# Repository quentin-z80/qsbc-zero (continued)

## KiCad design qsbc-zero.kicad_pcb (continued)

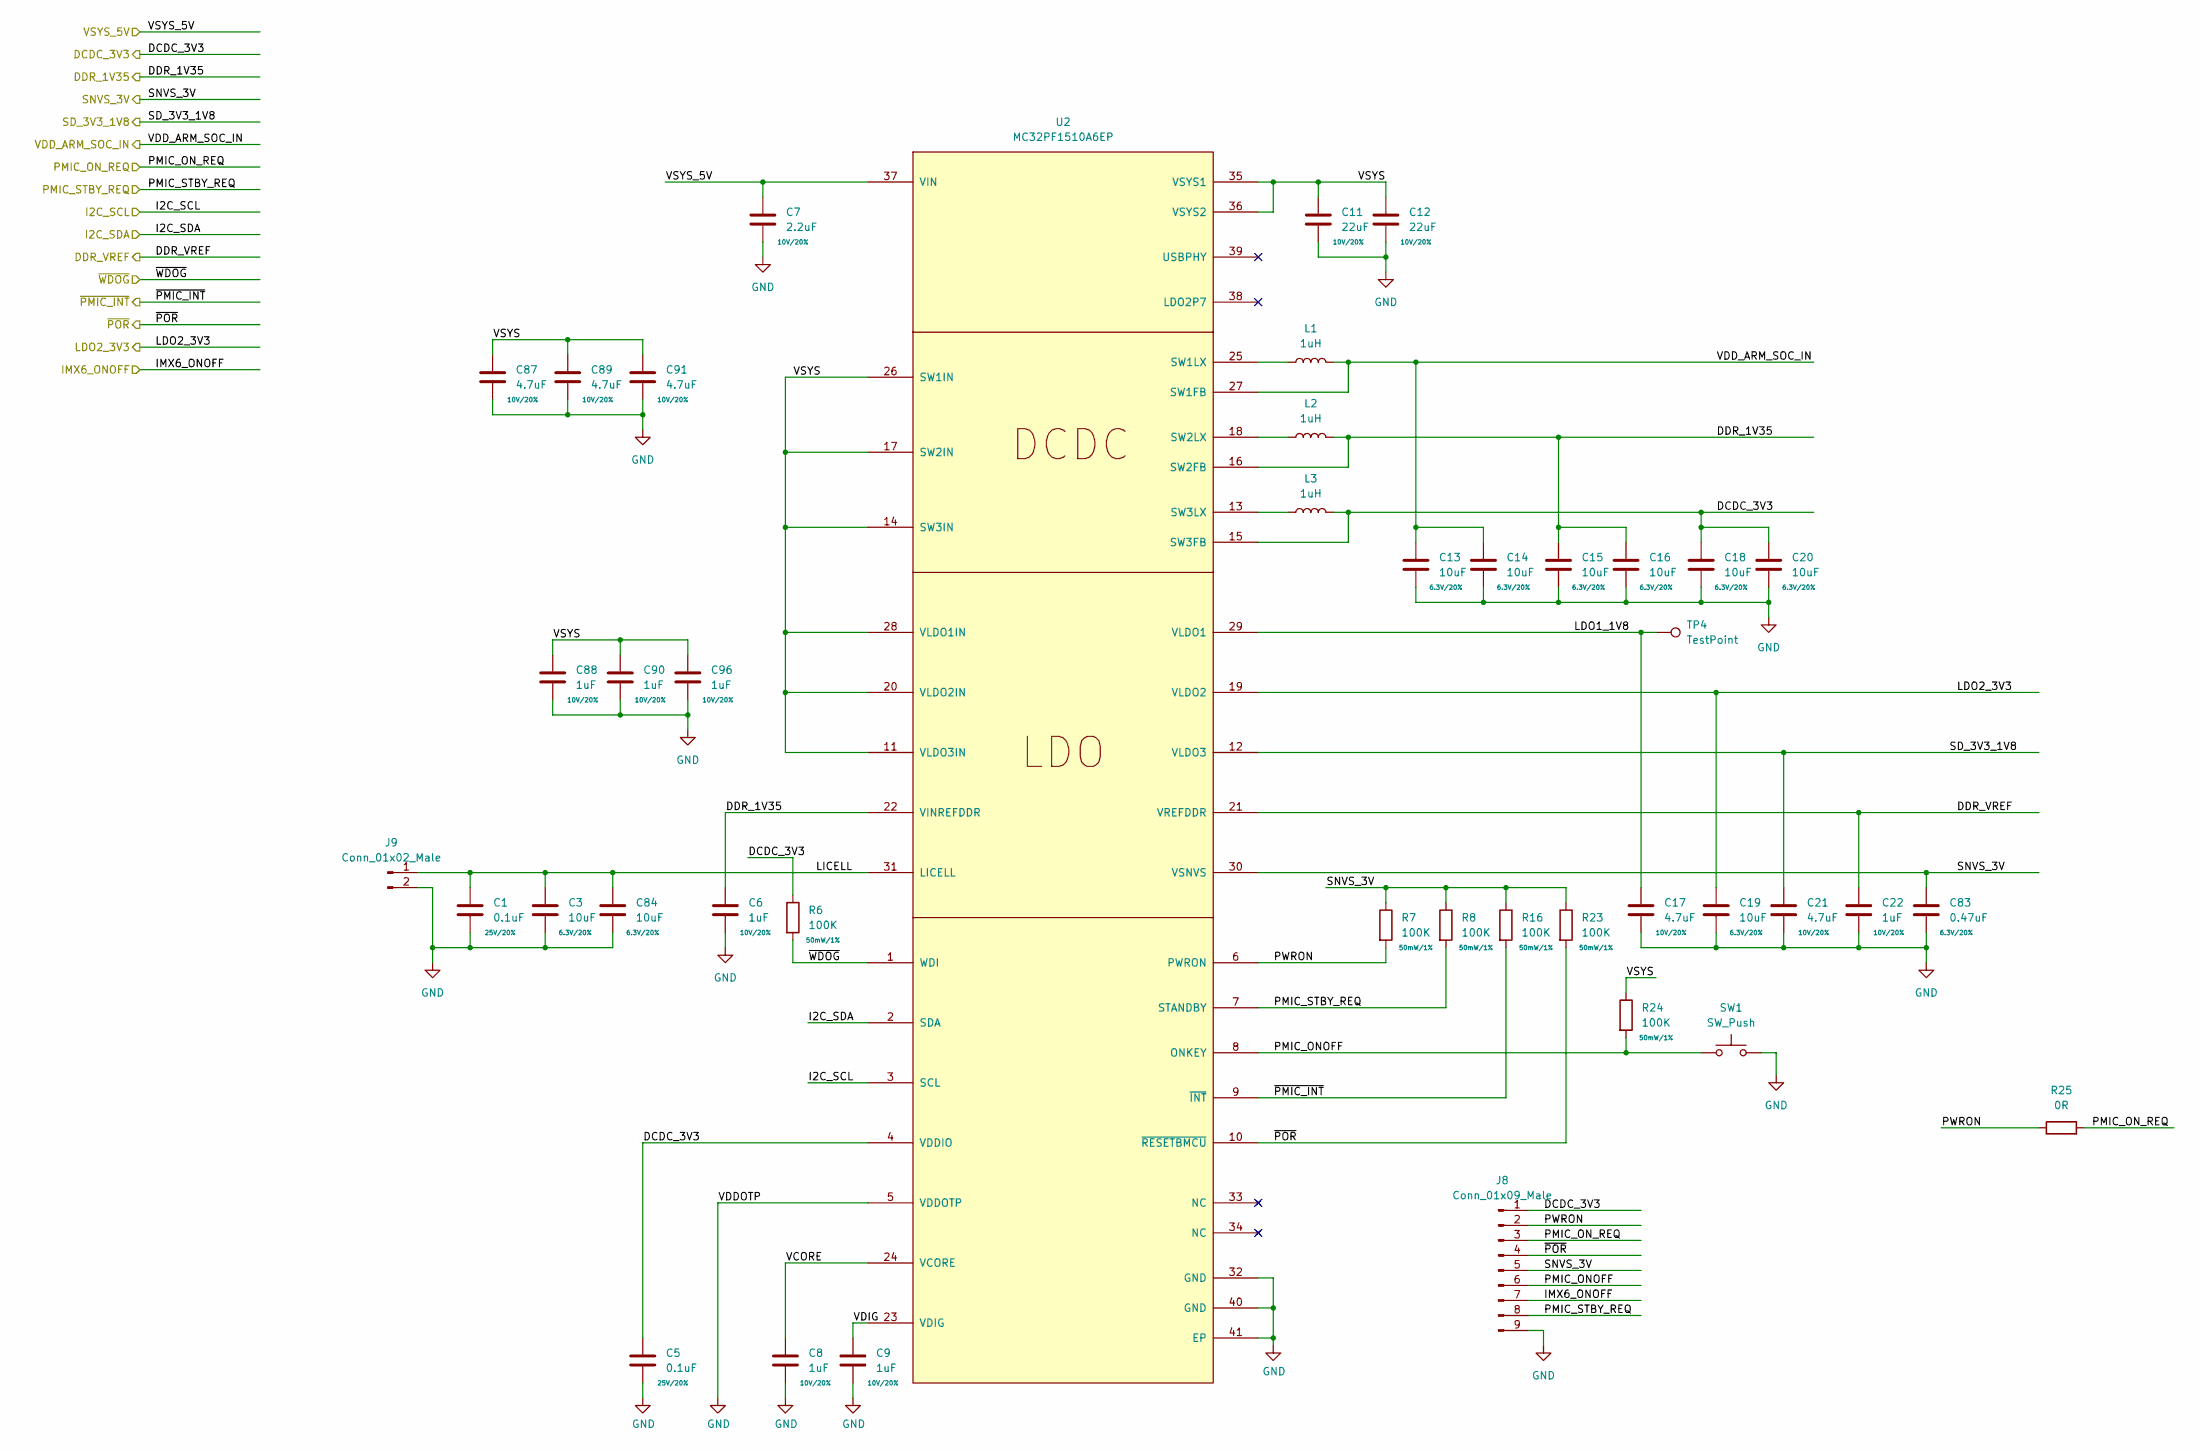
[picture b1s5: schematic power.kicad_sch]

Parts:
C1, C5: 0.1uF; C_0402_1005Metric; Rating 25V/20%; MPN GRM155R71E104KE14J; DigiKey_PN 490-14603-1-ND
C3, C13, C14, C15, C16, C18, C19, C20, C84: 10uF; C_0402_1005Metric; Rating 6.3V/20%; MPN GRM155R60J106ME05D; DigiKey_PN 490-GRM155R60J106ME05DCT-ND
C6, C8, C9, C22, C88, C90, C96: 1uF; C_0402_1005Metric; Rating 10V/20%; MPN GCM155C71A105KE38D; DigiKey_PN 490-13409-1-ND
C7: 2.2uF; C_0402_1005Metric; Rating 10V/20%; MPN CL05A225MP5NSNC; DigiKey_PN 1276-1467-1-ND
C11, C12: 22uF; C_0603_1608Metric; Rating 10V/20%; MPN CL10A226MP8NUNE; DigiKey_PN 1276-1274-1-ND
C17, C21, C87, C89, C91: 4.7uF; C_0402_1005Metric; Rating 10V/20%; MPN CL05A475MP5NRNC; DigiKey_PN 1276-1482-1-ND
C83: 0.47uF; C_0402_1005Metric; Rating 6.3V/20%; MPN CL05A474KQ5NNNC; DigiKey_PN 1276-1479-1-ND
J8: Conn_01x09_Male; PinHeader_1x09_P1.27mm_Vertical; MPN GRPB091VWVN-RC; DigiKey_PN S9014E-09-ND
J9: Conn_01x02_Male; PinHeader_1x02_P2.54mm_Vertical; MPN PRPC002SAAN-RC; DigiKey_PN S1011EC-02-ND
L1, L2, L3: 1uH; L_0603_1608Metric; MPN DFE18SBN1R0ME0L; DigiKey_PN 490-DFE18SBN1R0ME0LCT-ND
R6, R7, R8, R16, R23, R24: 100K; R_0402_1005Metric; Rating 50mW/1%; MPN CR0402-FX-1003GLF; DigiKey_PN CR0402-FX-1003GLFCT-ND
R25: 0R; R_0402_1005Metric; MPN RC0402FR-070RL; DigiKey_PN 311-0.0LRCT-ND
SW1: SW_Push; SW_Tactile_SPST_Angled_PTS645Vx58-2LFS; MPN PTS645VH58-2 LFS; DigiKey_PN CKN9120-ND
TP4: TestPoint; TestPoint_Pad_D1.0mm
U2: MC32PF1510A6EP; QFN-40-1EP_5x5mm_P0.4mm_EP3.8x3.8mm_ThermalVias; MPN MC32PF1510A6EP; DigiKey_PN MC32PF1510A6EP

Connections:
/Power/LDO1_1V8: C17.1, TP4.1, U2.29 (VLDO1)
/Power/LICELL: C1.1, C3.1, C84.1, J9.1, U2.31 (LICELL)
/Power/PMIC_ONOFF: J8.6, R24.2, SW1.2, U2.8 (ONKEY)
/Power/PWRON: J8.2, R7.2, R25.1, U2.6 (PWRON)
/Power/VCORE: C8.1, U2.24 (VCORE)
/Power/VDIG: C9.1, U2.23 (VDIG)
/Power/VSYS: C11.1, C12.1, C87.1, C88.1, C89.1, C90.1, C91.1, C96.1, R24.1, U2.11 (VLDO3IN), U2.14 (SW3IN), U2.17 (SW2IN), U2.20 (VLDO2IN), U2.26 (SW1IN), U2.28 (VLDO1IN), U2.35 (VSYS1), U2.36 (VSYS2)
/SNVS_3V3: C83.1, J8.5, R7.1, R8.1, R16.1, R23.1, U2.30 (VSNVS); also elsewhere on the board
DCDC_3V3: C5.1, C18.1, C20.1, J8.1, L3.2, R6.1, U2.4 (VDDIO), U2.15 (SW3FB); also elsewhere on the board
DDR_1V35: C6.1, C15.1, C16.1, L2.2, U2.16 (SW2FB), U2.22 (VINREFDDR); also elsewhere on the board
DDR_VREF: C22.1, U2.21 (VREFDDR); also elsewhere on the board
GND: C1.2, C3.2, C5.2, C6.2, C7.2, C8.2, C9.2, C11.2, C12.2, C13.2, C14.2, C15.2, C16.2, C17.2, C18.2, C19.2, C20.2, C21.2, C22.2, C83.2, C84.2, C87.2, C88.2, C89.2, C90.2, C91.2, C96.2, J8.9, J9.2, SW1.1, U2.5 (VDDOTP), U2.32 (GND), U2.40 (GND), U2.41 (EP); also elsewhere on the board
I2C4_SCL: U2.3 (SCL); also elsewhere on the board
I2C4_SDA: U2.2 (SDA); also elsewhere on the board
IMX6_ONOFF: J8.7; also elsewhere on the board
LDO2_3V3: C19.1, U2.19 (VLDO2); also elsewhere on the board
unnamed: L1.1, U2.25 (SW1LX)
unnamed: L2.1, U2.18 (SW2LX)
unnamed: L3.1, U2.13 (SW3LX)
PMIC_ON_REQ: J8.3, R25.2; also elsewhere on the board
PMIC_STBY_REQ: J8.8, R8.2, U2.7 (STANDBY); also elsewhere on the board
SD_3V3_1V8: C21.1, U2.12 (VLDO3); also elsewhere on the board
VDD_ARM_SOC_IN: C13.1, C14.1, L1.2, U2.27 (SW1FB); also elsewhere on the board
VSYS_5V: C7.1, U2.37 (VIN); also elsewhere on the board
~PMIC_INT: R16.2, U2.9 (~INT); also elsewhere on the board
~POR: J8.4, R23.2, U2.10 (~RESETBMCU); also elsewhere on the board
~WDOG: R6.2, U2.1 (WDI); also elsewhere on the board

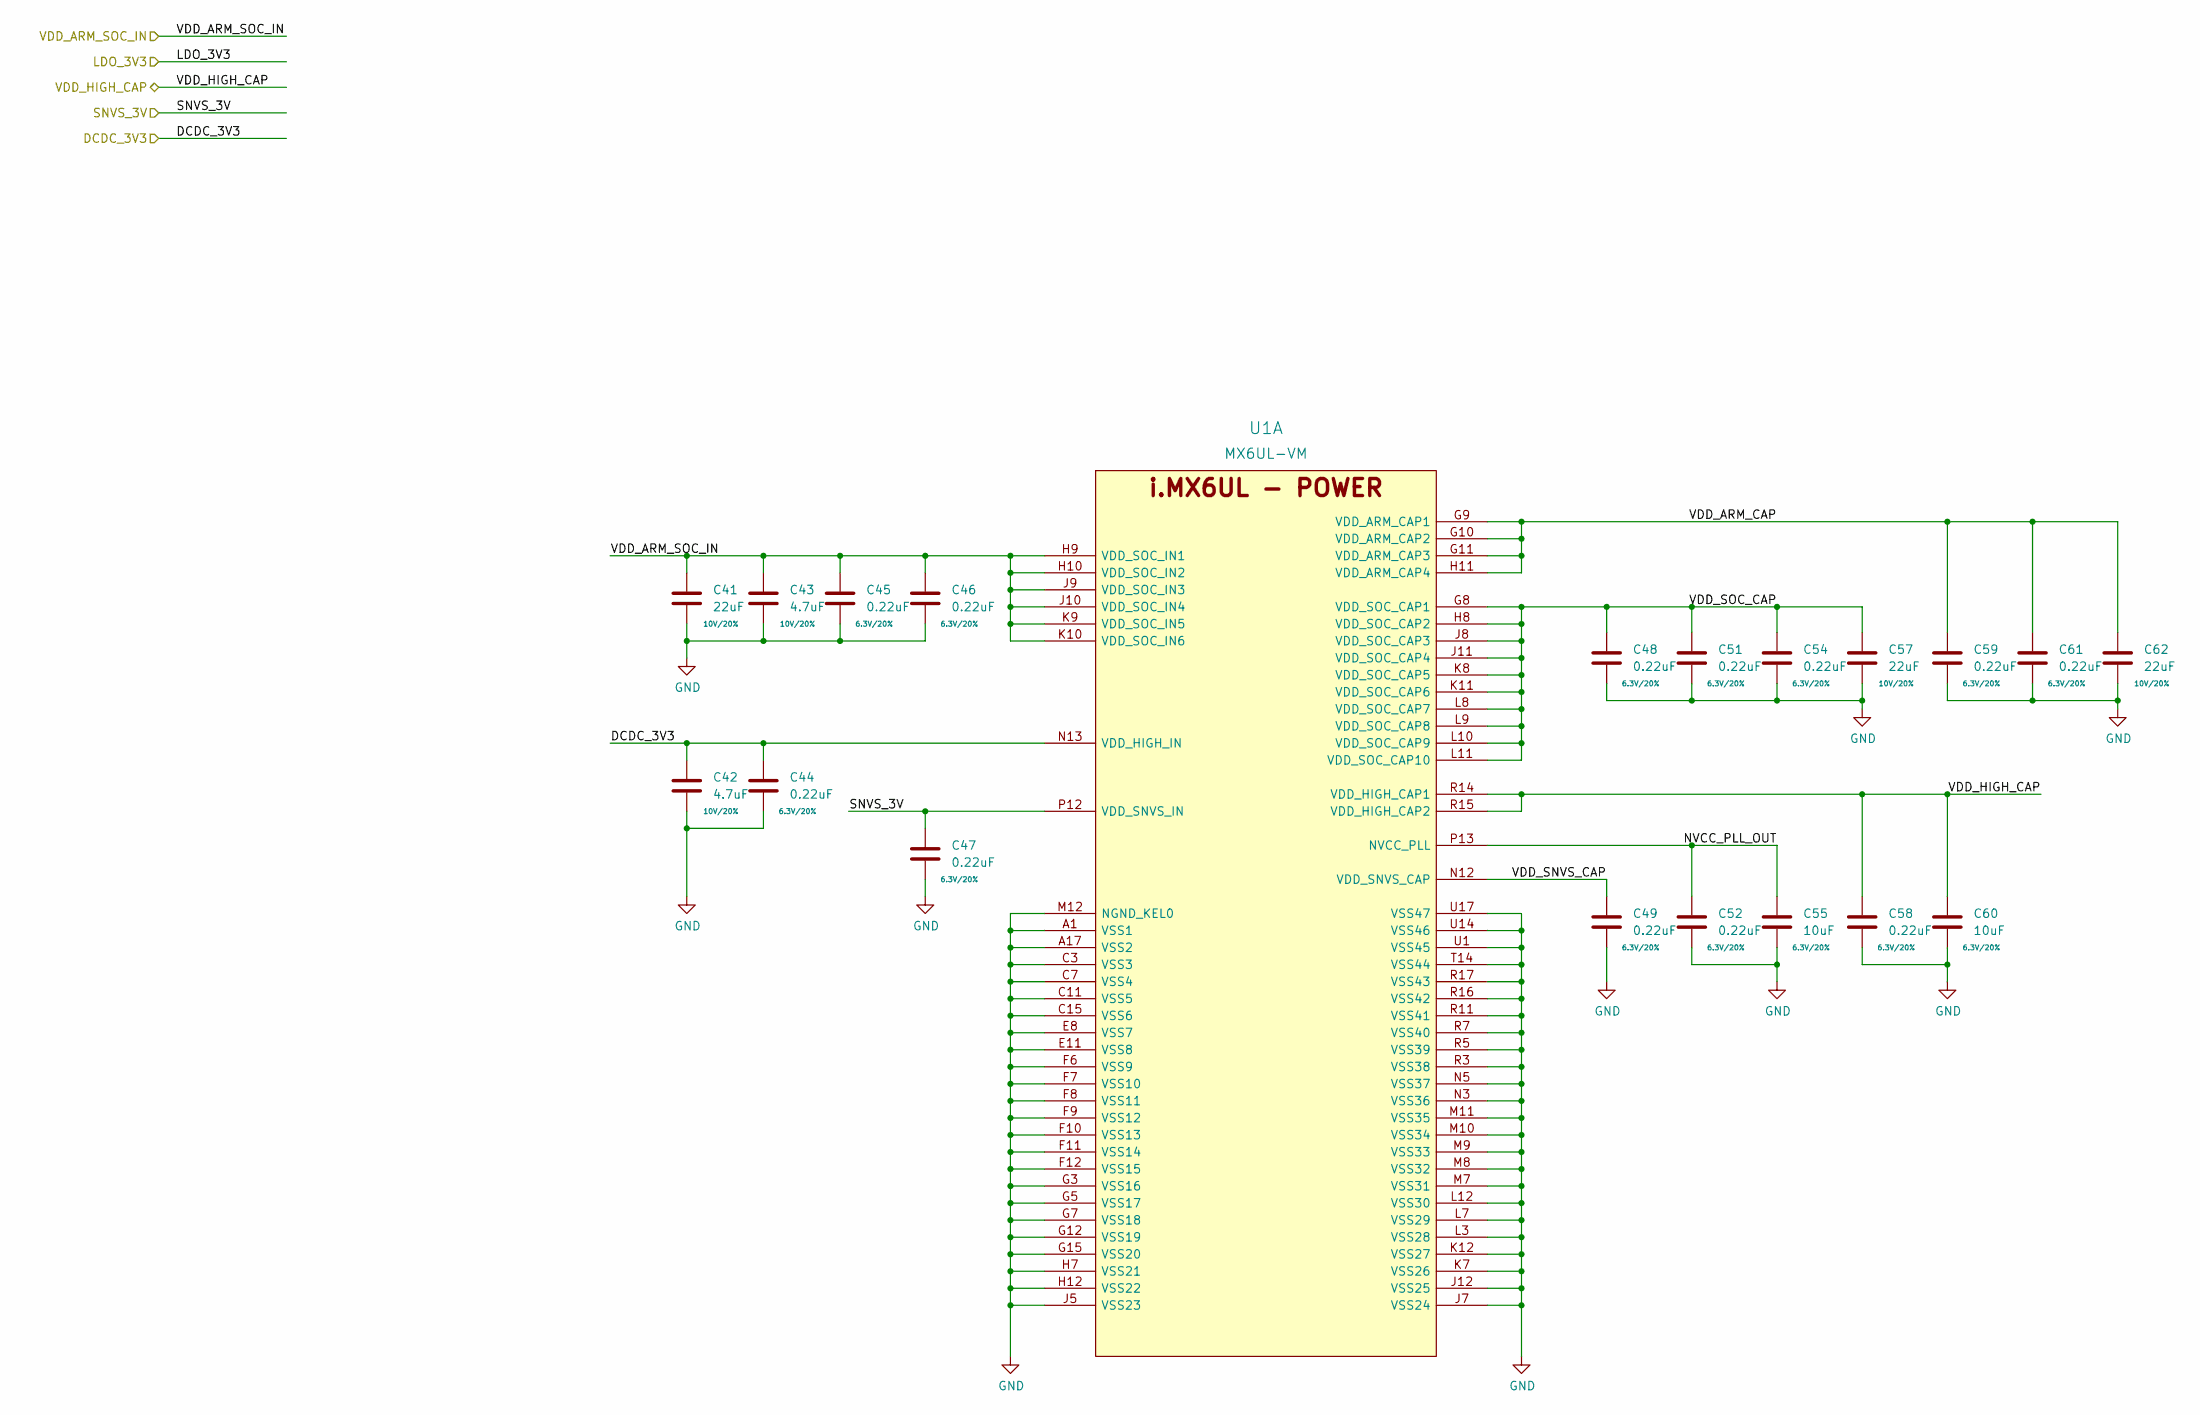
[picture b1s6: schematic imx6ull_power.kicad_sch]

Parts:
C41, C57, C62: 22uF; C_0603_1608Metric; Rating 10V/20%; MPN CL10A226MP8NUNE; DigiKey_PN 1276-1274-1-ND
C42, C43: 4.7uF; C_0402_1005Metric; Rating 10V/20%; MPN CL05A475MP5NRNC; DigiKey_PN 1276-1482-1-ND
C44, C45, C46, C47, C48, C49, C51, C52, C54, C58, C59, C61: 0.22uF; C_0201_0603Metric; Rating 6.3V/20%; MPN GRM033C80J224KE90D; DigiKey_PN 490-10392-1-ND
C55, C60: 10uF; C_0402_1005Metric; Rating 6.3V/20%; MPN GRM155R60J106ME05D; DigiKey_PN 490-GRM155R60J106ME05DCT-ND
U1: MX6UL-VM; SOT1534-2; MPN MCIMX6Y2DVM09AB; DigiKey_PN 568-14995-ND

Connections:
/IMX6ULL Power/NVCC_PLL_OUT: C52.1, C55.1, U1.P13 (NVCC_PLL)
/IMX6ULL Power/VDD_ARM_CAP: C59.1, C61.1, C62.1, U1.G9 (VDD_ARM_CAP1), U1.G10 (VDD_ARM_CAP2), U1.G11 (VDD_ARM_CAP3), U1.H11 (VDD_ARM_CAP4)
/IMX6ULL Power/VDD_SNVS_CAP: C49.1, U1.N12 (VDD_SNVS_CAP)
/IMX6ULL Power/VDD_SOC_CAP: C48.1, C51.1, C54.1, C57.1, U1.G8 (VDD_SOC_CAP1), U1.H8 (VDD_SOC_CAP2), U1.J8 (VDD_SOC_CAP3), U1.J11 (VDD_SOC_CAP4), U1.K8 (VDD_SOC_CAP5), U1.K11 (VDD_SOC_CAP6), U1.L8 (VDD_SOC_CAP7), U1.L9 (VDD_SOC_CAP8), U1.L10 (VDD_SOC_CAP9), U1.L11 (VDD_SOC_CAP10)
/SNVS_3V3: C47.1, U1.P12 (VDD_SNVS_IN); also elsewhere on the board
DCDC_3V3: C42.1, C44.1, U1.N13 (VDD_HIGH_IN); also elsewhere on the board
GND: C41.2, C42.2, C43.2, C44.2, C45.2, C46.2, C47.2, C48.2, C49.2, C51.2, C52.2, C54.2, C55.2, C57.2, C58.2, C59.2, C60.2, C61.2, C62.2, U1.A1 (VSS1), U1.A17 (VSS2), U1.C3 (VSS3), U1.C7 (VSS4), U1.C11 (VSS5), U1.C15 (VSS6), U1.E8 (VSS7), U1.E11 (VSS8), U1.F6 (VSS9), U1.F7 (VSS10), U1.F8 (VSS11), U1.F9 (VSS12), U1.F10 (VSS13), U1.F11 (VSS14), U1.F12 (VSS15), U1.G3 (VSS16), U1.G5 (VSS17), U1.G7 (VSS18), U1.G12 (VSS19), U1.G15 (VSS20), U1.H7 (VSS21), U1.H12 (VSS22), U1.J5 (VSS23), U1.J7 (VSS24), U1.J12 (VSS25), U1.K7 (VSS26), U1.K12 (VSS27), U1.L3 (VSS28), U1.L7 (VSS29), U1.L12 (VSS30), U1.M7 (VSS31), U1.M8 (VSS32), U1.M9 (VSS33), U1.M10 (VSS34), U1.M11 (VSS35), U1.M12 (NGND_KEL0), U1.N3 (VSS36), U1.N5 (VSS37), U1.R3 (VSS38), U1.R5 (VSS39), U1.R7 (VSS40), U1.R11 (VSS41), U1.R16 (VSS42), U1.R17 (VSS43), U1.T14 (VSS44), U1.U1 (VSS45), U1.U14 (VSS46), U1.U17 (VSS47); also elsewhere on the board
VDD_ARM_SOC_IN: C41.1, C43.1, C45.1, C46.1, U1.H9 (VDD_SOC_IN1), U1.H10 (VDD_SOC_IN2), U1.J9 (VDD_SOC_IN3), U1.J10 (VDD_SOC_IN4), U1.K9 (VDD_SOC_IN5), U1.K10 (VDD_SOC_IN6); also elsewhere on the board
VDD_HIGH_CAP: C58.1, C60.1, U1.R14 (VDD_HIGH_CAP1), U1.R15 (VDD_HIGH_CAP2); also elsewhere on the board

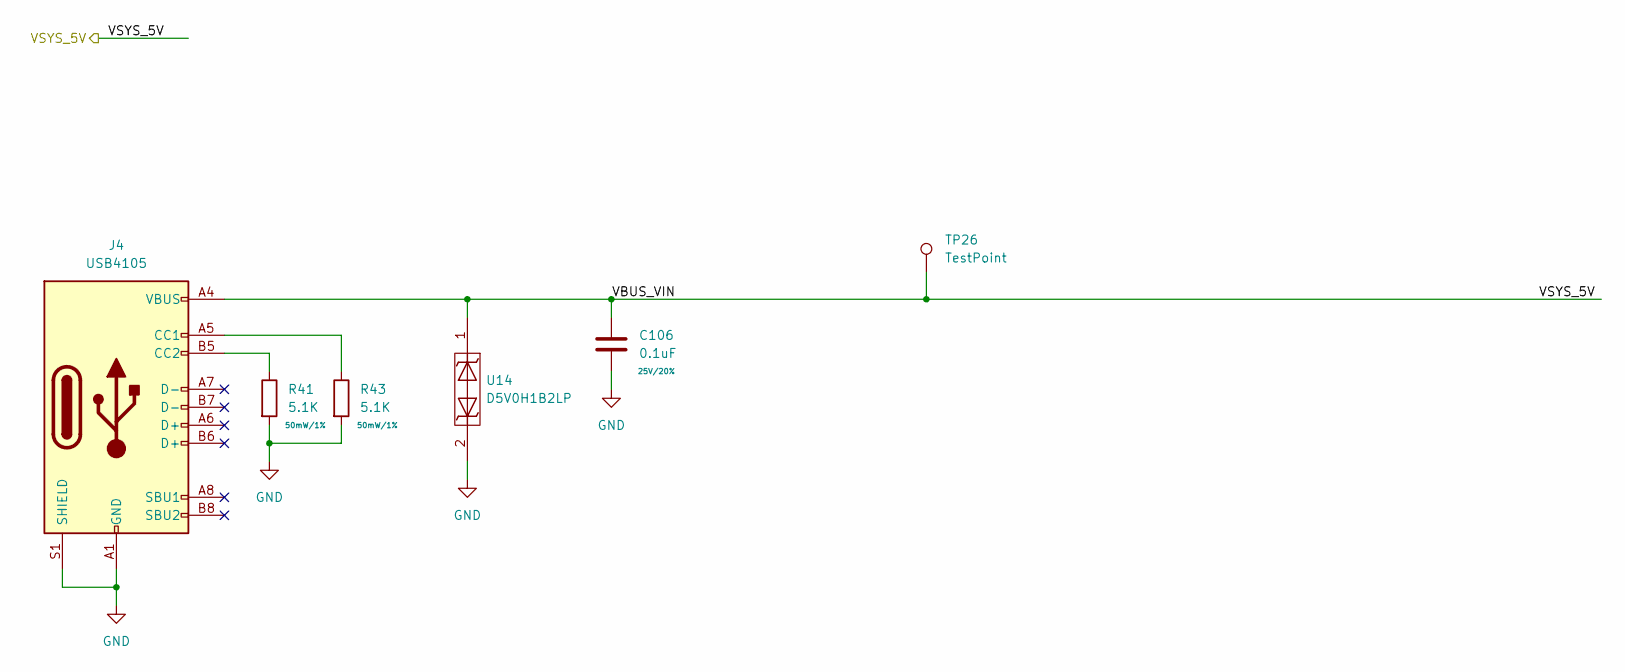
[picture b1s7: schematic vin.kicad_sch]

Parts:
C106: 0.1uF; C_0402_1005Metric; Rating 25V/20%; MPN GRM155R71E104KE14J; DigiKey_PN 490-14603-1-ND
J4: USB4105; USB_C_Receptacle_HRO_TYPE-C-31-M-12; MPN USB4105-GF-A; DigiKey_PN 2073-USB4105-GF-ACT-ND
R41, R43: 5.1K; R_0402_1005Metric; Rating 50mW/1%; MPN RC0402FR-075K1L; DigiKey_PN 311-5.10KLRCT-ND
TP26: TestPoint; TestPoint_Pad_D1.0mm
U14: D5V0H1B2LP; DFN100X60X45-2N; MPN D5V0H1B2LP-7B; DigiKey_PN D5V0H1B2LP-7BDICT-ND

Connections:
GND: C106.2, J4.A1 (GND), J4.A12 (GND), J4.B1 (GND), J4.B12 (GND), J4.S1 (SHIELD), R41.2, R43.2, U14.2; also elsewhere on the board
unnamed: J4.A5 (CC1), R43.1
unnamed: J4.B5 (CC2), R41.1
VSYS_5V: C106.1, J4.A4 (VBUS), J4.A9 (VBUS), J4.B4 (VBUS), J4.B9 (VBUS), TP26.1, U14.1; also elsewhere on the board

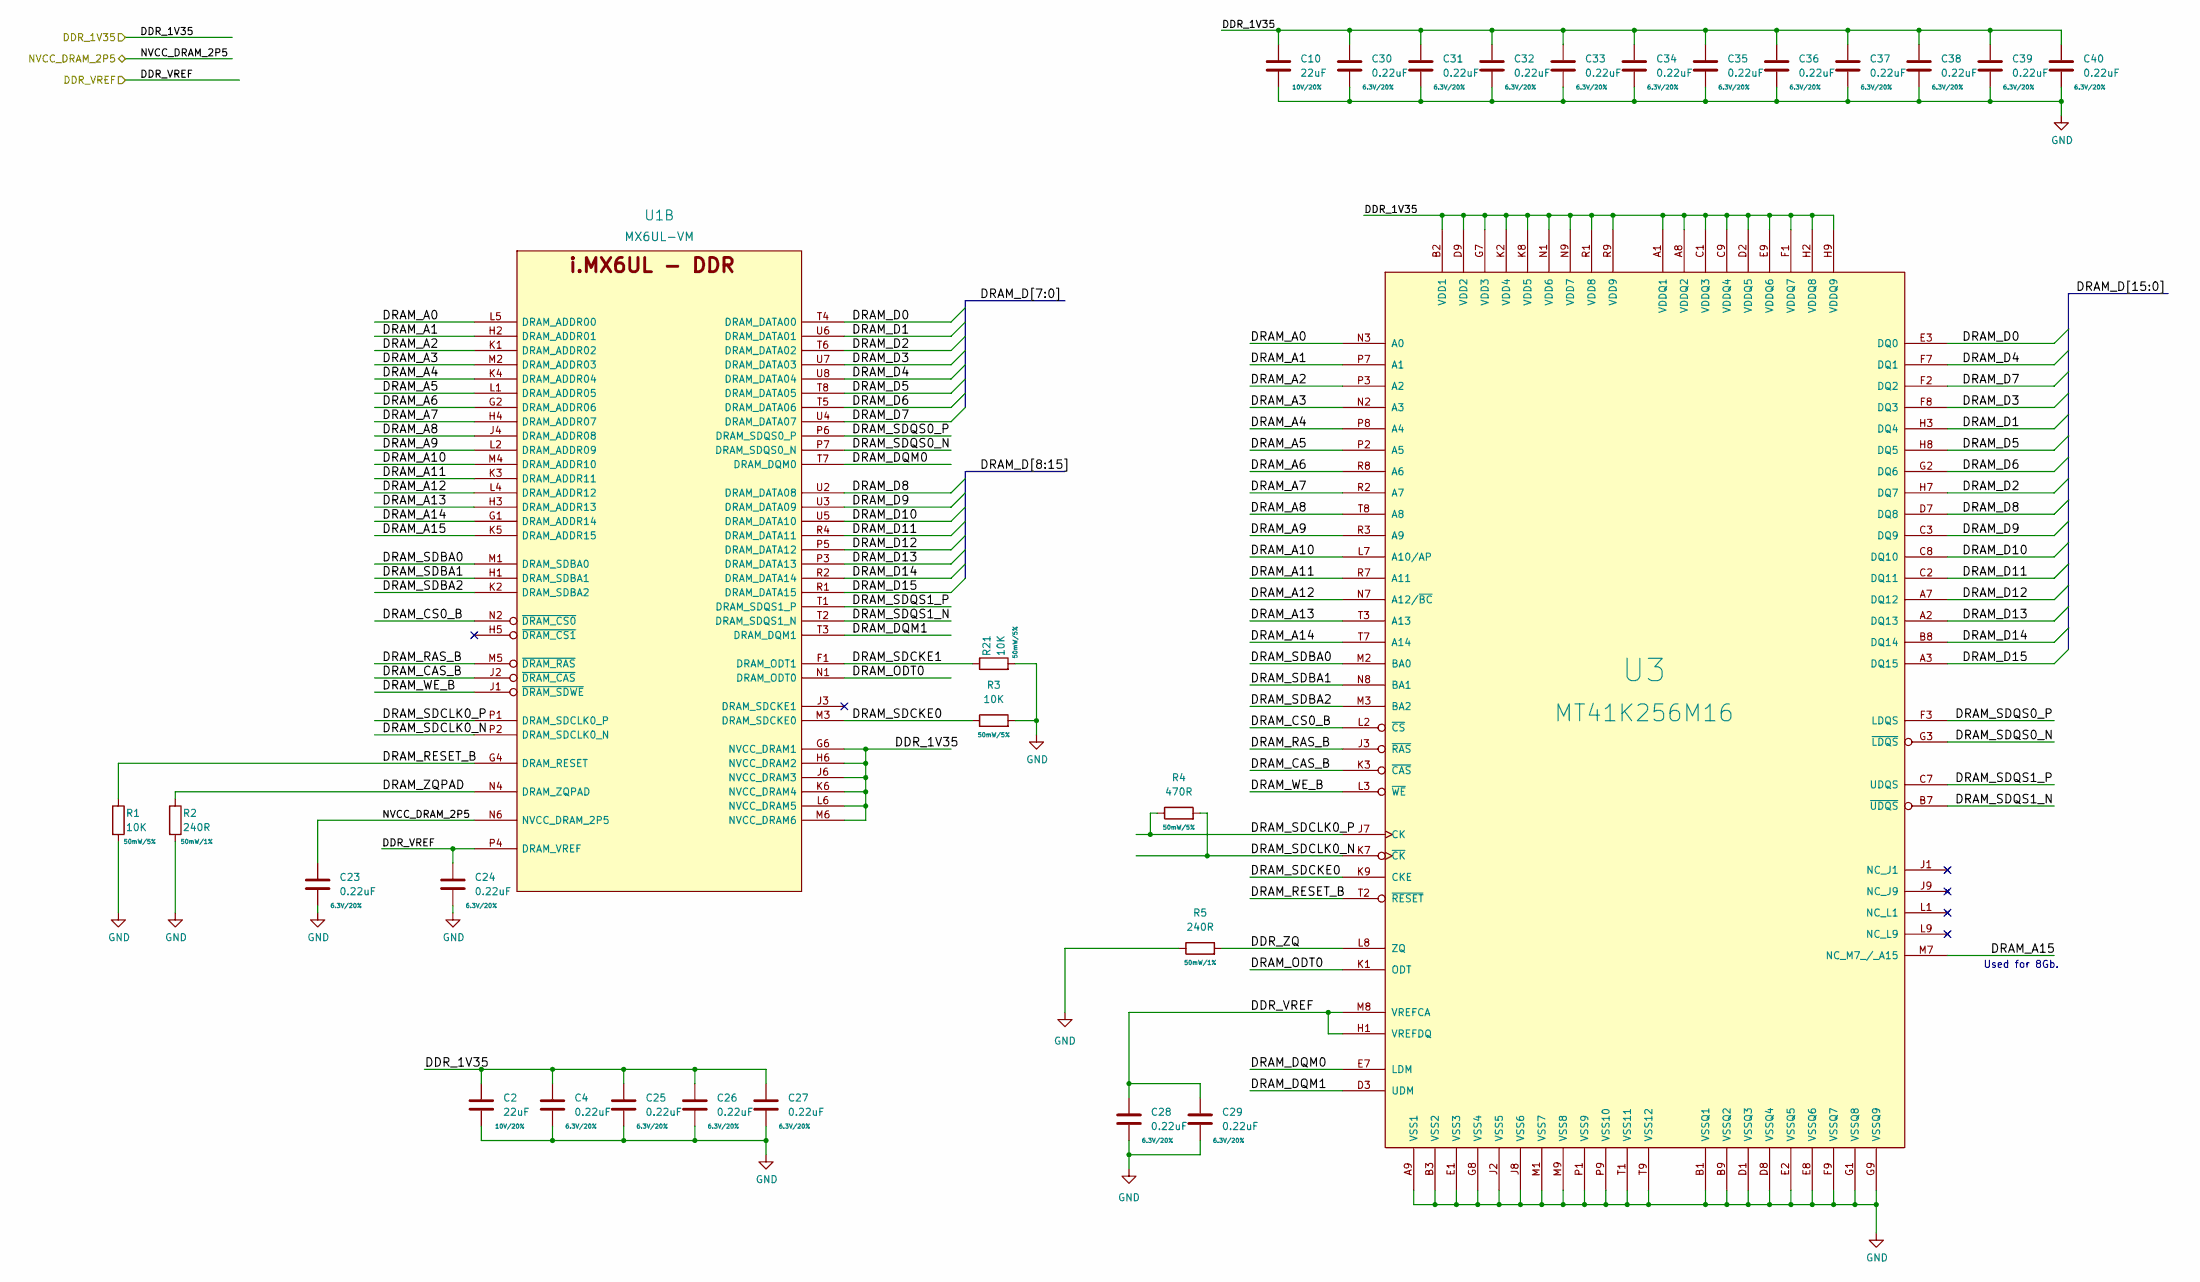
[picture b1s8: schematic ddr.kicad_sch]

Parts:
C2, C10: 22uF; C_0603_1608Metric; Rating 10V/20%; MPN CL10A226MP8NUNE; DigiKey_PN 1276-1274-1-ND
C4, C23, C24, C25, C26, C27, C28, C29, C30, C31, C32, C33, C34, C35, C36, C37, C38, C39, C40: 0.22uF; C_0201_0603Metric; Rating 6.3V/20%; MPN GRM033C80J224KE90D; DigiKey_PN 490-10392-1-ND
R1, R3, R21: 10K; R_0402_1005Metric; Rating 50mW/5%; MPN RC0402JR-0710KL; DigiKey_PN 311-10KJRCT-ND
R2, R5: 240R; R_0201_0603Metric; Rating 50mW/1%; MPN RC0201FR-07240RL; DigiKey_PN YAG2528CT-ND
R4: 470R; R_0201_0603Metric; Rating 50mW/5%; MPN RC0201JR-07470RL; DigiKey_PN 311-470NCT-ND
U1: MX6UL-VM; SOT1534-2; MPN MCIMX6Y2DVM09AB; DigiKey_PN 568-14995-ND
U3: MT41K256M16; MICRON-FBGA-96; MPN MT41K256M16TW-107:P; DigiKey_PN 557-1792-ND

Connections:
/DDR/DDR_ZQ: R5.2, U3.L8 (ZQ)
/DDR/DRAM_A0: U1.L5 (DRAM_ADDR00), U3.N3 (A0)
/DDR/DRAM_A1: U1.H2 (DRAM_ADDR01), U3.P7 (A1)
/DDR/DRAM_A2: U1.K1 (DRAM_ADDR02), U3.P3 (A2)
/DDR/DRAM_A3: U1.M2 (DRAM_ADDR03), U3.N2 (A3)
/DDR/DRAM_A4: U1.K4 (DRAM_ADDR04), U3.P8 (A4)
/DDR/DRAM_A5: U1.L1 (DRAM_ADDR05), U3.P2 (A5)
/DDR/DRAM_A6: U1.G2 (DRAM_ADDR06), U3.R8 (A6)
/DDR/DRAM_A7: U1.H4 (DRAM_ADDR07), U3.R2 (A7)
/DDR/DRAM_A8: U1.J4 (DRAM_ADDR08), U3.T8 (A8)
/DDR/DRAM_A9: U1.L2 (DRAM_ADDR09), U3.R3 (A9)
/DDR/DRAM_A10: U1.M4 (DRAM_ADDR10), U3.L7 (A10/AP)
/DDR/DRAM_A11: U1.K3 (DRAM_ADDR11), U3.R7 (A11)
/DDR/DRAM_A12: U1.L4 (DRAM_ADDR12), U3.N7 (A12/~BC)
/DDR/DRAM_A13: U1.H3 (DRAM_ADDR13), U3.T3 (A13)
/DDR/DRAM_A14: U1.G1 (DRAM_ADDR14), U3.T7 (A14)
/DDR/DRAM_A15: U1.K5 (DRAM_ADDR15), U3.M7 (NC_M7_/_A15)
/DDR/DRAM_CAS_B: U1.J2 (~DRAM_CAS), U3.K3 (~CAS)
/DDR/DRAM_CS0_B: U1.N2 (~DRAM_CS0), U3.L2 (~CS)
/DDR/DRAM_D0: U1.T4 (DRAM_DATA00), U3.E3 (DQ0)
/DDR/DRAM_D1: U1.U6 (DRAM_DATA01), U3.H3 (DQ4)
/DDR/DRAM_D2: U1.T6 (DRAM_DATA02), U3.H7 (DQ7)
/DDR/DRAM_D3: U1.U7 (DRAM_DATA03), U3.F8 (DQ3)
/DDR/DRAM_D4: U1.U8 (DRAM_DATA04), U3.F7 (DQ1)
/DDR/DRAM_D5: U1.T8 (DRAM_DATA05), U3.H8 (DQ5)
/DDR/DRAM_D6: U1.T5 (DRAM_DATA06), U3.G2 (DQ6)
/DDR/DRAM_D7: U1.U4 (DRAM_DATA07), U3.F2 (DQ2)
/DDR/DRAM_D8: U1.U2 (DRAM_DATA08), U3.D7 (DQ8)
/DDR/DRAM_D9: U1.U3 (DRAM_DATA09), U3.C3 (DQ9)
/DDR/DRAM_D10: U1.U5 (DRAM_DATA10), U3.C8 (DQ10)
/DDR/DRAM_D11: U1.R4 (DRAM_DATA11), U3.C2 (DQ11)
/DDR/DRAM_D12: U1.P5 (DRAM_DATA12), U3.A7 (DQ12)
/DDR/DRAM_D13: U1.P3 (DRAM_DATA13), U3.A2 (DQ13)
/DDR/DRAM_D14: U1.R2 (DRAM_DATA14), U3.B8 (DQ14)
/DDR/DRAM_D15: U1.R1 (DRAM_DATA15), U3.A3 (DQ15)
/DDR/DRAM_DQM0: U1.T7 (DRAM_DQM0), U3.E7 (LDM)
/DDR/DRAM_DQM1: U1.T3 (DRAM_DQM1), U3.D3 (UDM)
/DDR/DRAM_ODT0: U1.N1 (DRAM_ODT0), U3.K1 (ODT)
/DDR/DRAM_RAS_B: U1.M5 (~DRAM_RAS), U3.J3 (~RAS)
/DDR/DRAM_RESET_B: R1.1, U1.G4 (DRAM_RESET), U3.T2 (~RESET)
/DDR/DRAM_SDBA0: U1.M1 (DRAM_SDBA0), U3.M2 (BA0)
/DDR/DRAM_SDBA1: U1.H1 (DRAM_SDBA1), U3.N8 (BA1)
/DDR/DRAM_SDBA2: U1.K2 (DRAM_SDBA2), U3.M3 (BA2)
/DDR/DRAM_SDCKE0: R3.1, U1.M3 (DRAM_SDCKE0), U3.K9 (CKE)
/DDR/DRAM_SDCKE1: R21.1, U1.F1 (DRAM_ODT1)
/DDR/DRAM_SDCLK0_N: R4.2, U1.P2 (DRAM_SDCLK0_N), U3.K7 (~CK)
/DDR/DRAM_SDCLK0_P: R4.1, U1.P1 (DRAM_SDCLK0_P), U3.J7 (CK)
/DDR/DRAM_SDQS0_N: U1.P7 (DRAM_SDQS0_N), U3.G3 (~LDQS)
/DDR/DRAM_SDQS0_P: U1.P6 (DRAM_SDQS0_P), U3.F3 (LDQS)
/DDR/DRAM_SDQS1_N: U1.T2 (DRAM_SDQS1_N), U3.B7 (~UDQS)
/DDR/DRAM_SDQS1_P: U1.T1 (DRAM_SDQS1_P), U3.C7 (UDQS)
/DDR/DRAM_WE_B: U1.J1 (~DRAM_SDWE), U3.L3 (~WE)
/DDR/DRAM_ZQPAD: R2.1, U1.N4 (DRAM_ZQPAD)
DDR_1V35: C2.1, C4.1, C10.1, C25.1, C26.1, C27.1, C30.1, C31.1, C32.1, C33.1, C34.1, C35.1, C36.1, C37.1, C38.1, C39.1, C40.1, U1.G6 (NVCC_DRAM1), U1.H6 (NVCC_DRAM2), U1.J6 (NVCC_DRAM3), U1.K6 (NVCC_DRAM4), U1.L6 (NVCC_DRAM5), U1.M6 (NVCC_DRAM6), U3.A1 (VDDQ1), U3.A8 (VDDQ2), U3.B2 (VDD1), U3.C1 (VDDQ3), U3.C9 (VDDQ4), U3.D2 (VDDQ5), U3.D9 (VDD2), U3.E9 (VDDQ6), U3.F1 (VDDQ7), U3.G7 (VDD3), U3.H2 (VDDQ8), U3.H9 (VDDQ9), U3.K2 (VDD4), U3.K8 (VDD5), U3.N1 (VDD6), U3.N9 (VDD7), U3.R1 (VDD8), U3.R9 (VDD9); also elsewhere on the board
DDR_VREF: C24.1, C28.1, C29.1, U1.P4 (DRAM_VREF), U3.H1 (VREFDQ), U3.M8 (VREFCA); also elsewhere on the board
GND: C2.2, C4.2, C10.2, C23.2, C24.2, C25.2, C26.2, C27.2, C28.2, C29.2, C30.2, C31.2, C32.2, C33.2, C34.2, C35.2, C36.2, C37.2, C38.2, C39.2, C40.2, R1.2, R2.2, R3.2, R5.1, R21.2, U3.A9 (VSS1), U3.B1 (VSSQ1), U3.B3 (VSS2), U3.B9 (VSSQ2), U3.D1 (VSSQ3), U3.D8 (VSSQ4), U3.E1 (VSS3), U3.E2 (VSSQ5), U3.E8 (VSSQ6), U3.F9 (VSSQ7), U3.G1 (VSSQ8), U3.G8 (VSS4), U3.G9 (VSSQ9), U3.J2 (VSS5), U3.J8 (VSS6), U3.M1 (VSS7), U3.M9 (VSS8), U3.P1 (VSS9), U3.P9 (VSS10), U3.T1 (VSS11), U3.T9 (VSS12); also elsewhere on the board
VDD_HIGH_CAP: C23.1, U1.N6 (NVCC_DRAM_2P5); also elsewhere on the board

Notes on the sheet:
Used for 8Gb.

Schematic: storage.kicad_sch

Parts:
C74, C75: 0.22uF; C_0201_0603Metric; Rating 6.3V/20%; MPN GRM033C80J224KE90D; DigiKey_PN 490-10392-1-ND
C76: 10uF; C_0402_1005Metric; Rating 6.3V/20%; MPN GRM155R60J106ME05D; DigiKey_PN 490-GRM155R60J106ME05DCT-ND
C77, C78: 0.1uF; C_0402_1005Metric; Rating 25V/20%; MPN GRM155R71E104KE14J; DigiKey_PN 490-14603-1-ND
J1: Micro_SD_Card_Det1; GCT_MEM2051-00-195-00-A_REVC; MPN MEM2051-00-195-00-A; DigiKey_PN 2073-MEM2051-00-195-00-ACT-ND
J11: Conn_01x09_Male; PinHeader_1x09_P1.27mm_Vertical; MPN GRPB091VWVN-RC; DigiKey_PN S9014E-09-ND
R13: 10R; R_0402_1005Metric; Rating 50mW/5%; MPN RC0402JR-0710RL; DigiKey_PN 311-10JRCT-ND
R14, R15, R17: 10K; R_0402_1005Metric; Rating 50mW/5%; MPN RC0402JR-0710KL; DigiKey_PN 311-10KJRCT-ND
U1: MX6UL-VM; SOT1534-2; MPN MCIMX6Y2DVM09AB; DigiKey_PN 568-14995-ND
U8: D5V0H1B2LP; DFN100X60X45-2N; MPN D5V0H1B2LP-7B; DigiKey_PN D5V0H1B2LP-7BDICT-ND
U9: W25Q512JVEIQ; WSON-8-1EP_6x5mm_P1.27mm_EP3.4x4.3mm; MPN W25Q32JVZPIQ; DigiKey_PN W25Q32JVZPIQ-ND
U26, U27: TPD4EUSB30; USON-10_2.5x1.0mm_P0.5mm; MPN TPD4EUSB30DQAR; DigiKey_PN 296-28063-1-ND

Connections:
/Storage/ECSPI4_CS0: J11.7, U1.A5 (NAND_DATA07)
/Storage/ECSPI4_CS1: J11.8, U1.B7 (NAND_DATA01)
/Storage/ECSPI4_MISO: J11.6, U1.A6 (NAND_DATA06)
/Storage/ECSPI4_MOSI: J11.5, U1.B6 (NAND_DATA05)
/Storage/ECSPI4_SCLK: J11.4, U1.C6 (NAND_DATA04)
/Storage/QSPI_DATA0: U1.A3 (~NAND_READY), U9.5 (DI(IO0))
/Storage/QSPI_DATA1: U1.C5 (~NAND_CE0), U9.2 (DO(IO1))
/Storage/QSPI_DATA2: U1.B5 (~NAND_CE1), U9.3 (IO2)
/Storage/QSPI_DATA3: U1.A4 (NAND_CLE), U9.7 (IO3)
/Storage/QSPI_SCLK: U1.D5 (~NAND_WP), U9.6 (CLK)
/Storage/QSPI_nCS: R17.2, U1.E6 (NAND_DQS), U9.1 (~CS)
/Storage/SD1_CLK: J1.5 (CLK), R13.2, U27.2 (D1-), U27.9
/Storage/SD1_CLK_R: R13.1, U1.C1 (SD1_CLK)
/Storage/SD1_CMD: J1.3 (CMD), R15.2, U1.C2 (SD1_CMD), U27.1 (D1+), U27.10
/Storage/SD1_DATA0: J1.7 (DAT0), R14.2, U1.B3 (SD1_DATA0), U26.2 (D1-), U26.9
/Storage/SD1_DATA1: J1.8 (DAT1), U1.B2 (SD1_DATA1), U26.1 (D1+), U26.10
/Storage/SD1_DATA2: J1.1 (DAT2), U1.B1 (SD1_DATA2), U26.5 (D2-), U26.6
/Storage/SD1_DATA3: J1.2 (DAT3/CD), U1.A2 (SD1_DATA3), U26.4 (D2+), U26.7
DCDC_3V3: C74.1, C76.1, C77.1, C78.1, J1.4 (VDD), J11.1, R17.1, U1.E7 (NVCC_NAND), U8.1, U9.8 (VCC); also elsewhere on the board
GND: C74.2, C75.2, C76.2, C77.2, C78.2, J1.6 (VSS), J1.9 (SHIELD), J11.9, U8.2, U9.4 (GND), U9.9 (EP), U26.3 (GND), U26.8 (GND), U27.3 (GND), U27.8 (GND); also elsewhere on the board
I2C2_SCL: J11.2; also elsewhere on the board
I2C2_SDA: J11.3; also elsewhere on the board
SD1_CD: J1.10 (DET), U27.4 (D2+), U27.7; also elsewhere on the board
SD_3V3_1V8: C75.1, R14.1, R15.1, U1.C4 (NVCC_SD1); also elsewhere on the board

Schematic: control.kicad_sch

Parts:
C50: 0.22uF; C_0201_0603Metric; Rating 6.3V/20%; MPN GRM033C80J224KE90D; DigiKey_PN 490-10392-1-ND
C70, C71: 16pF; C_0402_1005Metric; Rating 50V/1%; MPN GCM1555C1H160JA16D; DigiKey_PN 490-GCM1555C1H160JA16DCT-ND
C72, C73: 18pF; C_0402_1005Metric; Rating 50V/5%; MPN CC0402JRNPO9BN180; DigiKey_PN 311-1415-1-ND
J7: Conn_01x06_Male; Harwin_M20-89006xx_1x06_P2.54mm_Horizontal; MPN M20-8900605; DigiKey_PN 952-3267-ND
JP1, JP2: Jumper_2_Open; SolderJumper-2_P1.3mm_Open_RoundedPad1.0x1.5mm
R12: 2.2M; R_0402_1005Metric; Rating 50mW/1%; MPN RC0402FR-132M2L; DigiKey_PN 13-RC0402FR-132M2LCT-ND
R20, R139, R140: 10K; R_0402_1005Metric; Rating 50mW/5%; MPN RC0402JR-0710KL; DigiKey_PN 311-10KJRCT-ND
TP3: TestPoint; TestPoint_Pad_D1.0mm
U1: MX6UL-VM; SOT1534-2; MPN MCIMX6Y2DVM09AB; DigiKey_PN 568-14995-ND
Y1: 24Mhz; Crystal_SMD_3225-4Pin_3.2x2.5mm; MPN ECS-240-9-33B-CWN-TR; DigiKey_PN XC2477CT-ND
Y2: 32.768kHz; Crystal_SMD_3215-2Pin_3.2x1.5mm; MPN CM315D32768EZFT; DigiKey_PN 300-8816-1-ND

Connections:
/Control/BOOT_MODE0: JP2.1 (A), U1.T10 (BOOT_MODE0)
/Control/BOOT_MODE1: JP1.1 (A), U1.U10 (BOOT_MODE1)
/Control/RTC_XTALI: C72.1, U1.T11 (RTC_XTALI), Y2.1
/Control/RTC_XTALO: C73.1, U1.U11 (RTC_XTALO), Y2.2
/Control/UART1_CTS: TP3.1, U1.K15 (~UART1_CTS)
/Control/UART1_RTS: J7.2, U1.J14 (~UART1_RTS)
/Control/UART1_RX: J7.4, U1.K16 (UART1_RX_DATA)
/Control/UART1_TX: J7.5, U1.K14 (UART1_TX_DATA)
/Control/XTALI: C70.1, R12.1, U1.T16 (XTALI), Y1.3
/Control/XTALO: C71.1, U1.T17 (XTALO), Y1.1
/SNVS_3V3: R139.1, R140.1; also elsewhere on the board
DCDC_3V3: C50.1, U1.H13 (NVCC_UART); also elsewhere on the board
GND: C50.2, C70.2, C71.2, C72.2, C73.2, J7.1, R12.2, R20.2, U1.N7 (TEST_MODE), Y1.2, Y1.4; also elsewhere on the board
GPIO1_IO10: U1.M14 (JTAG_TCK); also elsewhere on the board
GPIO1_IO11: U1.P14 (JTAG_TMS); also elsewhere on the board
GPIO1_IO12: U1.N16 (JTAG_TDI); also elsewhere on the board
GPIO1_IO13: U1.N15 (JTAG_TDO); also elsewhere on the board
GPIO1_IO14: U1.N14 (~JTAG_TRST); also elsewhere on the board
GPIO1_IO15: R20.1, U1.P15 (JTAG_MOD); also elsewhere on the board
GPIO1_IO20: U1.J17 (UART2_TX_DATA); also elsewhere on the board
GPIO1_IO21: U1.J16 (UART2_RX_DATA); also elsewhere on the board
GPIO1_IO22: U1.J15 (~UART2_CTS); also elsewhere on the board
GPIO1_IO23: U1.H14 (~UART2_RTS); also elsewhere on the board
GPIO1_IO24: U1.H17 (UART3_TX_DATA); also elsewhere on the board
GPIO1_IO25: U1.H16 (UART3_RX_DATA); also elsewhere on the board
GPIO1_IO26: U1.H15 (~UART3_CTS); also elsewhere on the board
GPIO1_IO27: U1.G14 (~UART3_RTS); also elsewhere on the board
GPIO1_IO28: U1.G17 (UART4_TX_DATA); also elsewhere on the board
GPIO1_IO29: U1.G16 (UART4_RX_DATA); also elsewhere on the board
GPIO1_IO30: U1.F17 (UART5_TX_DATA); also elsewhere on the board
GPIO1_IO31: U1.G13 (UART5_RX_DATA); also elsewhere on the board
IMX6_ONOFF: U1.R8 (ONOFF); also elsewhere on the board
unnamed: JP1.2 (B), R139.2
unnamed: JP2.2 (B), R140.2
PMIC_ON_REQ: U1.T9 (SNVS_PMIC_ON_REQ); also elsewhere on the board
PMIC_STBY_REQ: U1.U9 (CCM_PMIC_STBY_REQ); also elsewhere on the board
~PMIC_INT: U1.R10 (SNVS_TAMPER0); also elsewhere on the board
~POR: U1.P8 (~POR); also elsewhere on the board

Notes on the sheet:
BOOT_MODE[1:0] 00 - Boot from Fuses 01 - Serial Downloader 10 - Internal Boot 11 - Reserved
